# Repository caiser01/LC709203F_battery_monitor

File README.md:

# LC709203F LiPo Fuel Gauge #

The ON Semiconductor LC709203F Battery Fuel Gauge is an IC for monitoring the charge state of a single lithium ion cell. The IC communicates over an I2C bus and provides the battery's relative state-of-charge (RSOC) and voltage. The LC709203F can also determine battery temperature if an optional external thermistor is attached to the battery. It can also provide an alarm output signal if the battery charge or voltage is below a threshold set by the user.

More information is available from ON Semiconductor:
[LC709203F: Battery Fuel Gauge for 1-Cell Lithium-Ion/Polymer](https://www.onsemi.com/products/power-management/battery-management/battery-fuel-gauges/lc709203f)

## Respository Contents ##
* **/Firmware** - Arduino example and driver
* **/Hardware** - Eagle PCB files for a simple test board

### Software Used ###

* EAGLE 7.7
* Arduino 1.8.5

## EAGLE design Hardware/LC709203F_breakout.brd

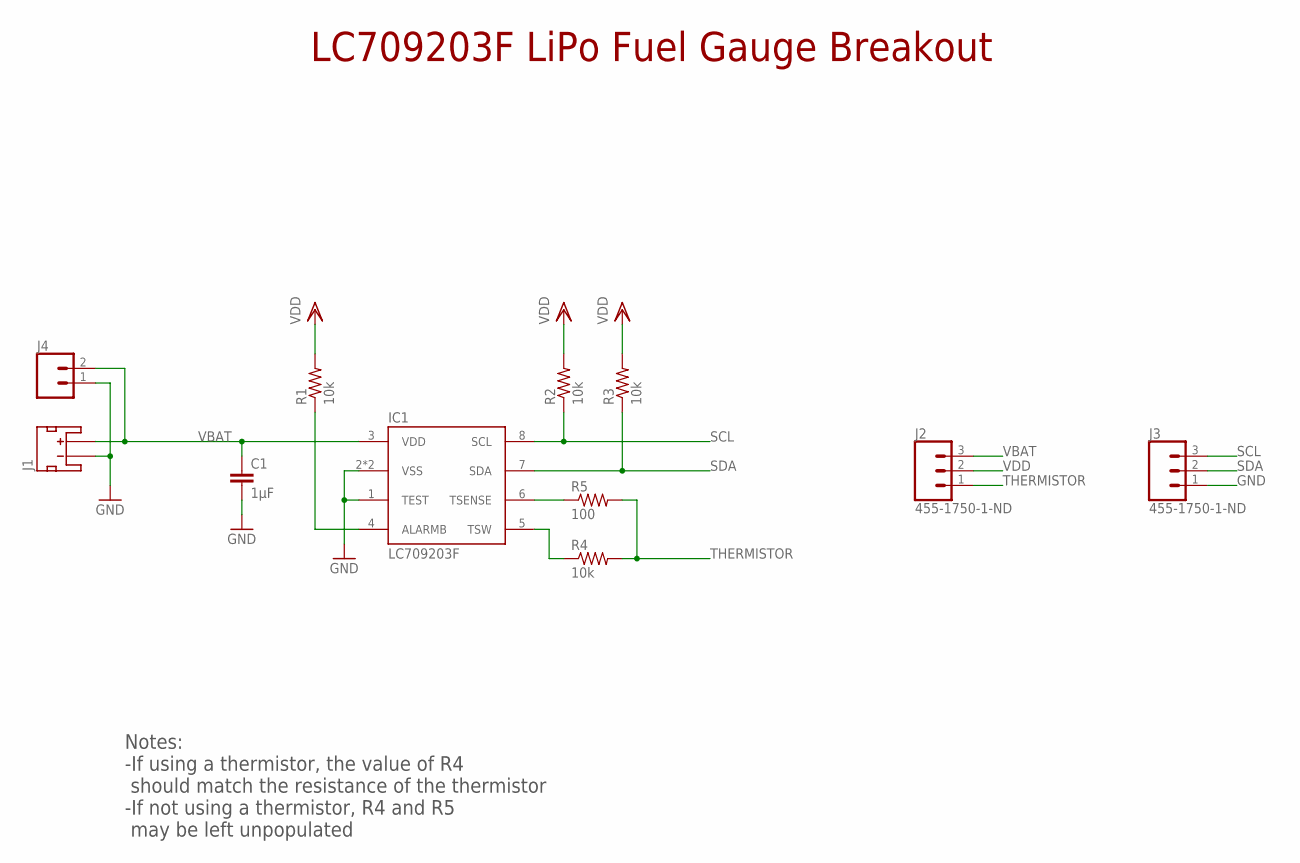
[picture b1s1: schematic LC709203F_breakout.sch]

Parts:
C1: 1µF; C0805
IC1: LC709203F; WDFN8_ONSEMI
J1: S2B-PH-SM4-TB; JST-2-SMD
J2, J3: 455-1750-1-ND; 1X03
J4: CONN_02; 1X02
R1, R2, R3, R4: 10k; R0805
R5: 100; R0805

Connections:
GND: C1.2, IC1.1 (TEST), IC1.2 (VSS), IC1.9 (VSS), J1.1 (-), J3.1, J4.1
unnamed: IC1.4 (ALARMB), R1.1
unnamed: IC1.6 (TSENSE), R5.1
unnamed: IC1.5 (TSW), R4.1
SCL: IC1.8 (SCL), J3.3, R2.1
SDA: IC1.7 (SDA), J3.2, R3.1
THERMISTOR: J2.1, R4.2, R5.2
VBAT: C1.1, IC1.3 (VDD), J1.2 (+), J2.3, J4.2
VDD: J2.2, R1.2, R2.2, R3.2

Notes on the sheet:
LC709203F LiPo Fuel Gauge Breakout
Notes: -If using a thermistor, the value of R4 should match the resistance of the thermistor -If not using a thermistor, R4 and R5 may be left unpopulated

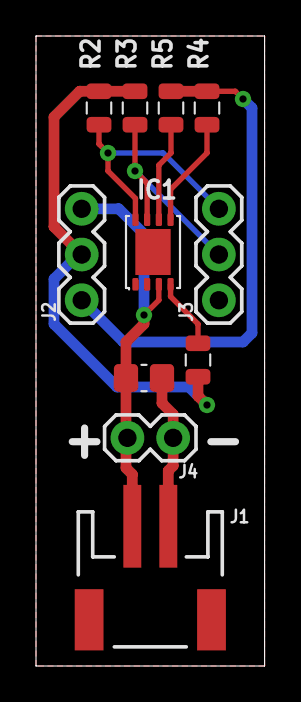
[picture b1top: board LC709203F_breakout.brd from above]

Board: 4 copper layers, 12.7 x 35.0 mm, 11 parts (0 on the bottom side), 9 nets.

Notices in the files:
parts and their libraries:
SparkFun-Connectors: Licensing: Creative Commons ShareAlike 4.0 International - https://creativecommons.org/licenses/by-sa/4.0
